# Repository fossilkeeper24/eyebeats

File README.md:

# Eyebeats

A heart rate sensor that lights up upon switching it on and then displays your heart rate on a screen from your finger. 

> from [hermes](https://hermes.hackclub.com/steps/step5.html)

## PCB

### Front

### Back

## Schematic

## What did I learn from this?

I learnt a little bit about I2C communication between components. I also learnt how to make my own kicad schematic symbol for components that I could not find the symbol for online.

> I also learnt the importance of time management skills and that it is not a good idea to try to complete a project with a deadline the day before it is due in. Especially when the concepts are completely new to me and would require more research than a concept I am already familiar with.

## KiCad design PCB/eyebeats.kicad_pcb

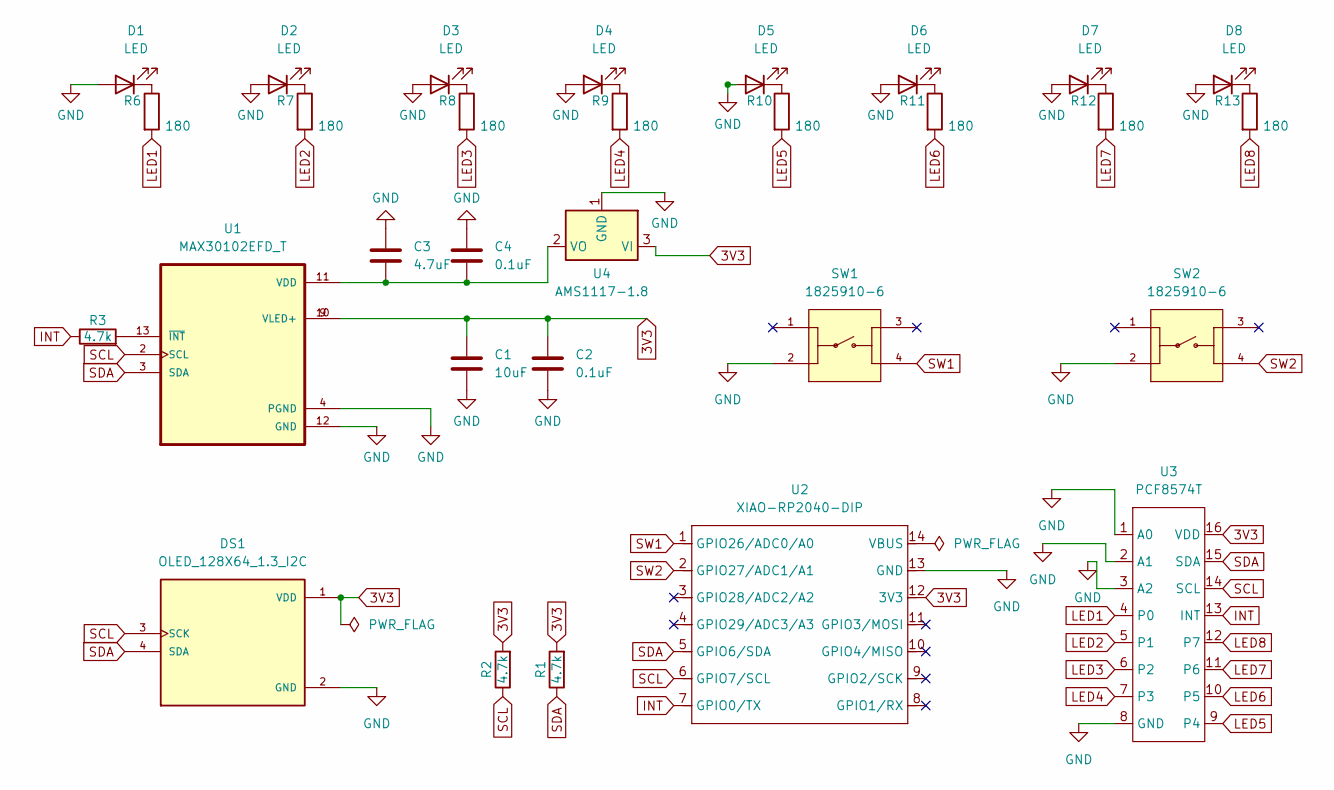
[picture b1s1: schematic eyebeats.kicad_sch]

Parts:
C1: 10uF; CAPC2012X94N
C2, C4: 0.1uF; CAPC2012X94N
C3: 4.7uF; CAPC2012X94N
D1, D2, D3, D4, D5, D6, D7, D8: LED; LED_D3.0mm_Clear
DS1: OLED_128X64_1.3_I2C; LCD_OLED_128X64_1.3_I2C; PARTREV NA
R1, R2, R3: 4.7k; R_Axial_DIN0204_L3.6mm_D1.6mm_P5.08mm_Horizontal
R6, R7, R8, R9, R10, R11, R12, R13: 180; R_Axial_DIN0204_L3.6mm_D1.6mm_P5.08mm_Horizontal
SW1, SW2: 1825910-6; SW_1825910-6-4; PARTREV C10
U1: MAX30102EFD_T; XDCR_MAX30101EFD_
U2: XIAO-RP2040-DIP
U3: PCF8574T; SOIC-16W_7.5x10.3mm_P1.27mm
U4: AMS1117-1.8; SOT-223-3_TabPin2

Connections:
3V3: C1.2, C2.2, DS1.1 (VDD), R1.2, R2.2, U1.9 (VLED+), U1.10 (VLED+), U2.12 (3V3), U3.16 (VDD), U4.3 (VI); also elsewhere on the board
GND: C1.1, C2.1, C3.2, C4.2, D1.2 (A), D2.2 (A), D3.2 (A), D4.2 (A), D5.2 (A), D6.2 (A), D7.2 (A), D8.2 (A), DS1.2 (GND), SW1.2, SW2.2, U1.4 (PGND), U1.12 (GND), U2.13 (GND), U3.1 (A0), U3.2 (A1), U3.3 (A2), U3.8 (GND), U4.1 (GND); also elsewhere on the board
INT: R3.1, U2.7 (GPIO0/TX), U3.13 (INT)
LED1: R6.2, U3.4 (P0)
LED2: R7.2, U3.5 (P1)
LED3: R8.2, U3.6 (P2)
LED4: R9.2, U3.7 (P3)
LED5: R10.2, U3.9 (P4)
LED6: R11.2, U3.10 (P5)
LED7: R12.2, U3.11 (P6)
LED8: R13.2, U3.12 (P7)
unnamed: D1.1 (K), R6.1
unnamed: D2.1 (K), R7.1
unnamed: D3.1 (K), R8.1
unnamed: D4.1 (K), R9.1
unnamed: D5.1 (K), R10.1
unnamed: D6.1 (K), R11.1
unnamed: D7.1 (K), R12.1
unnamed: D8.1 (K), R13.1
unnamed: C3.1, C4.1, U1.11 (VDD), U4.2 (VO)
unnamed: R3.2, U1.13 (~INT)
SCL: DS1.3 (SCK), R2.1, U1.2 (SCL), U2.6 (GPIO7/SCL), U3.14 (SCL); also elsewhere on the board
SDA: DS1.4 (SDA), R1.1, U1.3 (SDA), U2.5 (GPIO6/SDA), U3.15 (SDA); also elsewhere on the board
SW1: SW1.4, U2.1 (GPIO26/ADC0/A0); also elsewhere on the board
SW2: SW2.4, U2.2 (GPIO27/ADC1/A1); also elsewhere on the board

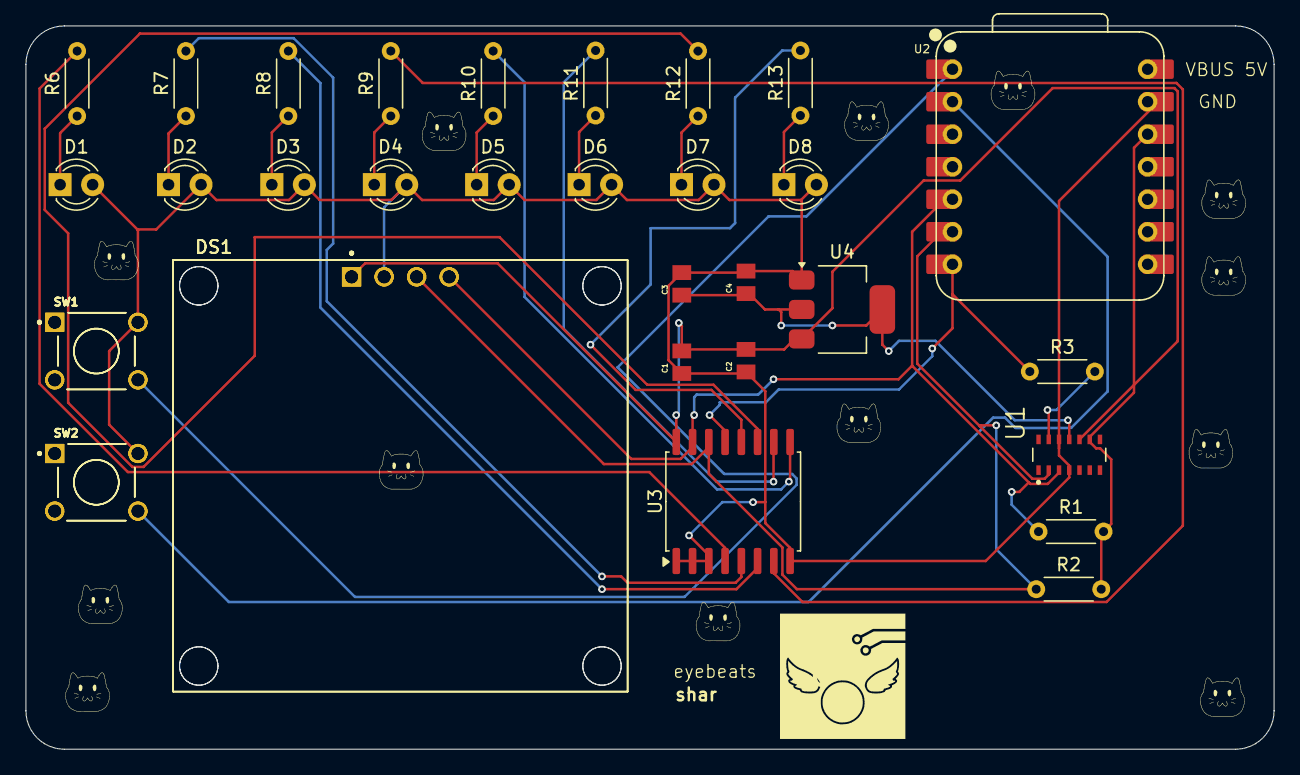
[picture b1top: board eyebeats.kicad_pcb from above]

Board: 2 copper layers, 97.5 x 56.5 mm, 33 parts (0 on the bottom side), 25 nets.

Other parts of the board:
DS1#2: OLED_128X64_1.3_I2C; LCD_OLED_128X64_1.3_I2C
SW1#2, SW2#2: 1825910-6; SW_1825910-6-4

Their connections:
3V3: DS1#2.1 (VDD); also elsewhere on the board
GND: DS1#2.2 (GND), SW1#2.2, SW2#2.2; also elsewhere on the board
SCL: DS1#2.3 (SCK); also elsewhere on the board
SDA: DS1#2.4 (SDA); also elsewhere on the board
SW1: SW1#2.4; also elsewhere on the board
SW2: SW2#2.4; also elsewhere on the board

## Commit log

2025-08-02 Initial adding files
2025-08-02 added datasheet for oled segment
2025-08-02 added code to configure sensor
2025-08-02 edited led directions in pcb and more codeee
2025-08-02 fixed io expandor initialisation
2025-08-02 added in example code of oled
2025-08-02 removed unnecessary comments and made more use of oled display
2025-08-03 drill gerbr
2025-08-03 Update README.md add an img
2025-08-03 added a description
2025-08-03 added more pcb imgs
2025-08-03 Added more imgs and description in the README
